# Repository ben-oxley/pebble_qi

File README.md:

# pebble_qi
Pebble QI watchstrap

Currently designing for a 50mA charge current.

Would work well with these pogo pins http://www.peaktest.co.uk/probe/p695 (4mm long)

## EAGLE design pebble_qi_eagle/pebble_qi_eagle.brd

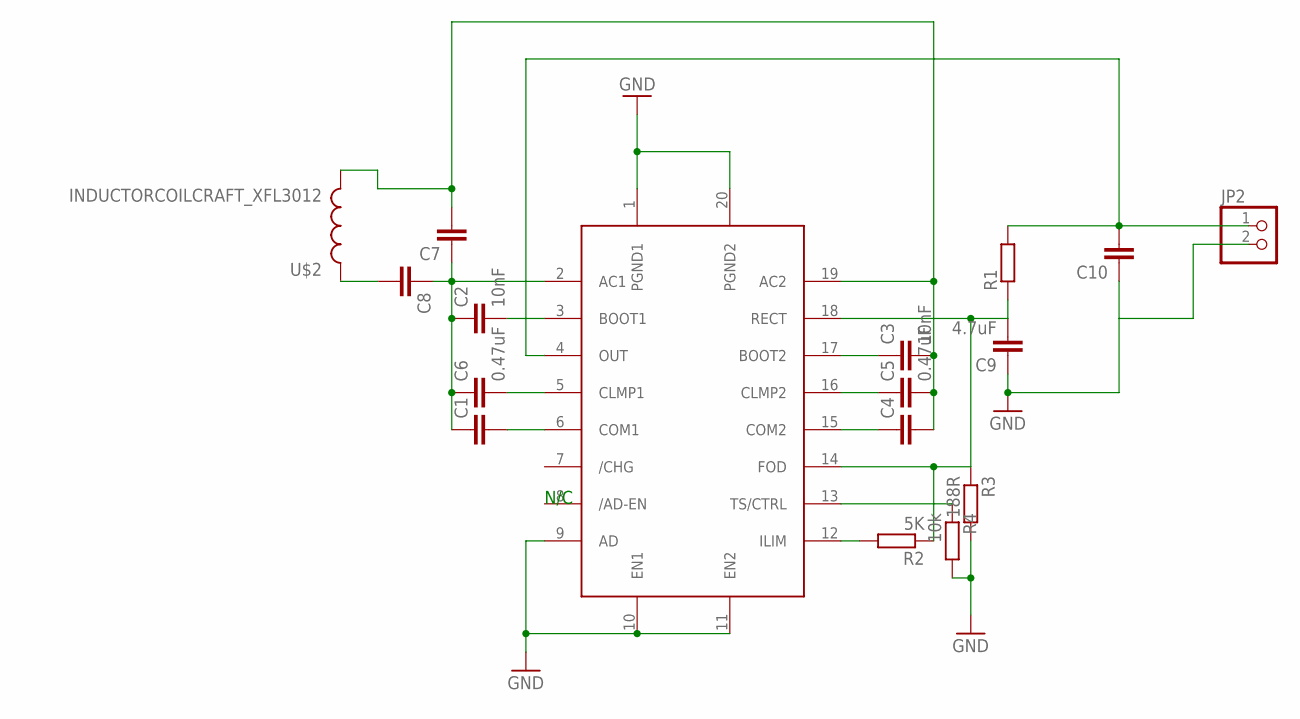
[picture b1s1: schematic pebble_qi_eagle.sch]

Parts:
C1, C4, C7, C8, C10: C-EUC0603; C0603
C2, C3: 10nF; C0603
C5, C6: 0.47uF; C0603
C9: 4.7uF; C0603
JP2: PINHD-1X2/90; 1X02/90
R1: R-EU_R0603; R0603
R2: 5K; R0603
R3: 188R; R0603
R4: 10k; R0603
U$1: BQ51013B; QFNRHL20
U$2: INDUCTORCOILCRAFT_XFL3012; COILCRAFT_XFL3012

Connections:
GND: C9.1, C10.1, JP2.2, R3.2, R4.2, U$1.1 (PGND1), U$1.9 (AD), U$1.10 (EN1), U$1.11 (EN2), U$1.20 (PGND2)
unnamed: C3.2, C4.2, C5.2, C7.2, U$1.19 (AC2), U$2.P$2 (2)
unnamed: C1.1, C2.1, C6.1, C7.1, C8.1, U$1.2 (AC1)
unnamed: C2.2, U$1.3 (BOOT1)
unnamed: C6.2, U$1.5 (CLMP1)
unnamed: C1.2, U$1.6 (COM1)
unnamed: R4.1, U$1.13 (TS/CTRL)
unnamed: C8.2, U$2.P$1 (1)
unnamed: C4.1, U$1.15 (COM2)
unnamed: C5.1, U$1.16 (CLMP2)
unnamed: C3.1, U$1.17 (BOOT2)
unnamed: C9.2, R1.1, R2.1, R3.1, U$1.14 (FOD), U$1.18 (RECT)
unnamed: C10.2, JP2.1, R1.2, U$1.4 (OUT)
unnamed: R2.2, U$1.12 (ILIM)

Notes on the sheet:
N/C

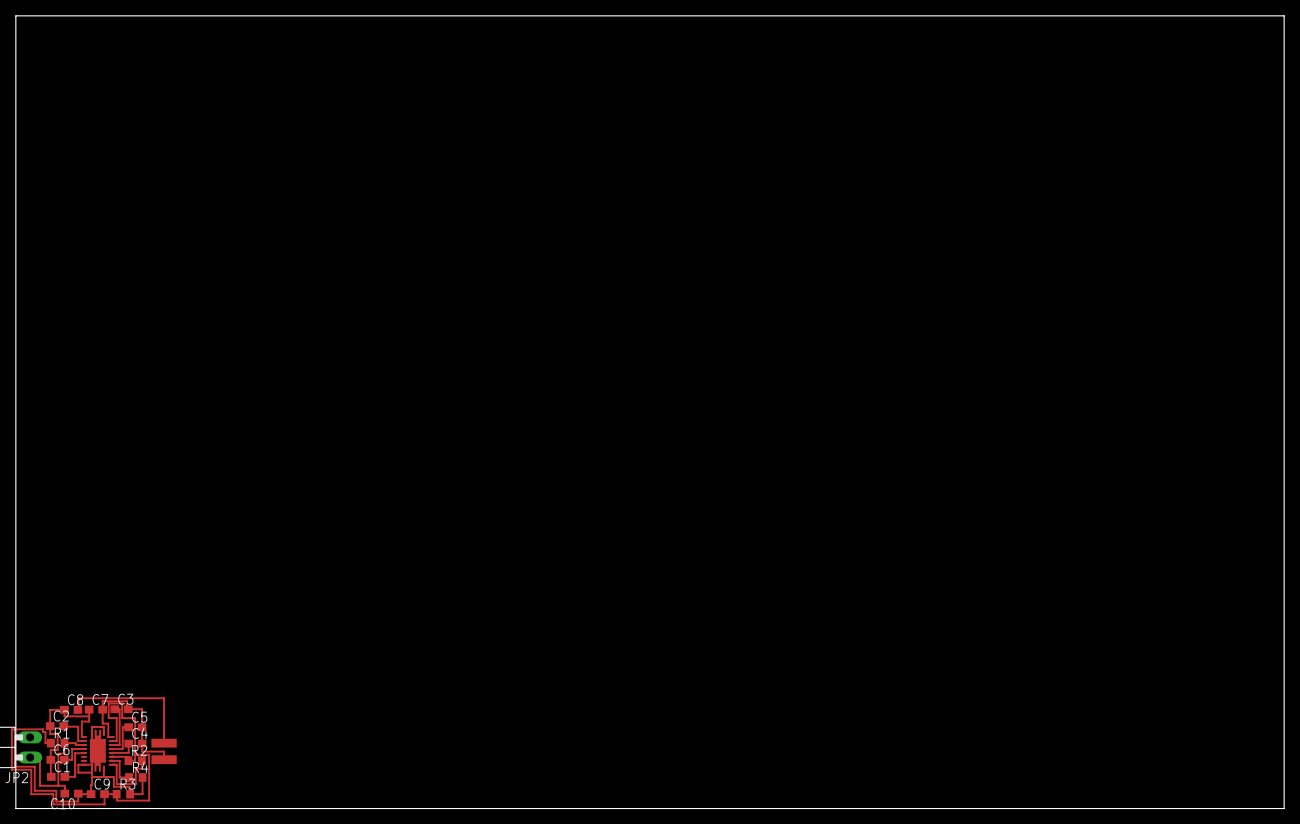
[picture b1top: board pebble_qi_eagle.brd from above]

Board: 2 copper layers, 160.0 x 100.0 mm, 17 parts (0 on the bottom side), 14 nets.

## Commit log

2015-10-31 Started schematic
2015-10-31 Updated schematic with values and updated read me
2015-10-31 Created starter board layout
2015-11-01 Initial routing
